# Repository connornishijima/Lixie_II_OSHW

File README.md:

# Lixie II Open Hardware
Want to make your own Lixie II? You're in the right place. This repository is a work in progress, but everything you need like the 3D printed base kit, Eagle PCB files or CAD files are here already!

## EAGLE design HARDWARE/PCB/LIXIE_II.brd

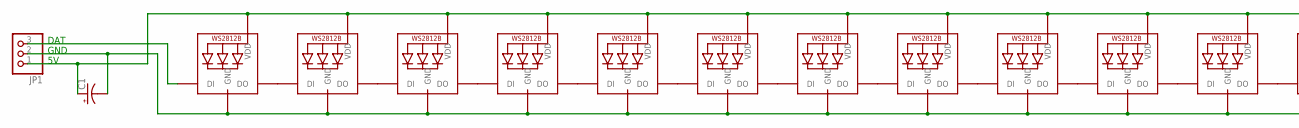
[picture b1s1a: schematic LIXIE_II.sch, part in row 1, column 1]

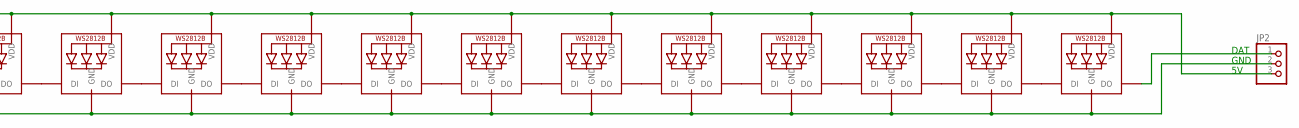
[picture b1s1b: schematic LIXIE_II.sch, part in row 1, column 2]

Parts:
C1: CPOL-USE5-10.5; E5-10,5
JP1, JP2: PINHD-1X3; 1X03
LED1, LED2, LED3, LED4, LED5, LED6, LED7, LED8, LED9, LED10, LED11, LED12, LED13, LED14, LED15, LED16, LED17, LED18, LED19, LED20, LED21, LED22: WS2812B_5050N; WS2812B-NARROW

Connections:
5V: C1.+, JP1.1, JP2.3, LED1.1-VDD (VDD), LED2.1-VDD (VDD), LED3.1-VDD (VDD), LED4.1-VDD (VDD), LED5.1-VDD (VDD), LED6.1-VDD (VDD), LED7.1-VDD (VDD), LED8.1-VDD (VDD), LED9.1-VDD (VDD), LED10.1-VDD (VDD), LED11.1-VDD (VDD), LED12.1-VDD (VDD), LED13.1-VDD (VDD), LED14.1-VDD (VDD), LED15.1-VDD (VDD), LED16.1-VDD (VDD), LED17.1-VDD (VDD), LED18.1-VDD (VDD), LED19.1-VDD (VDD), LED20.1-VDD (VDD), LED21.1-VDD (VDD), LED22.1-VDD (VDD)
GND: C1.-, JP1.2, JP2.2, LED1.3-GND (GND), LED2.3-GND (GND), LED3.3-GND (GND), LED4.3-GND (GND), LED5.3-GND (GND), LED6.3-GND (GND), LED7.3-GND (GND), LED8.3-GND (GND), LED9.3-GND (GND), LED10.3-GND (GND), LED11.3-GND (GND), LED12.3-GND (GND), LED13.3-GND (GND), LED14.3-GND (GND), LED15.3-GND (GND), LED16.3-GND (GND), LED17.3-GND (GND), LED18.3-GND (GND), LED19.3-GND (GND), LED20.3-GND (GND), LED21.3-GND (GND), LED22.3-GND (GND)
unnamed: JP1.3, LED1.4-DIN (DI)
unnamed: LED1.2-DOUT (DO), LED2.4-DIN (DI)
unnamed: LED2.2-DOUT (DO), LED3.4-DIN (DI)
unnamed: LED3.2-DOUT (DO), LED4.4-DIN (DI)
unnamed: LED4.2-DOUT (DO), LED5.4-DIN (DI)
unnamed: LED5.2-DOUT (DO), LED6.4-DIN (DI)
unnamed: LED6.2-DOUT (DO), LED7.4-DIN (DI)
unnamed: LED7.2-DOUT (DO), LED8.4-DIN (DI)
unnamed: LED8.2-DOUT (DO), LED9.4-DIN (DI)
unnamed: LED9.2-DOUT (DO), LED10.4-DIN (DI)
unnamed: LED10.2-DOUT (DO), LED11.4-DIN (DI)
unnamed: LED11.2-DOUT (DO), LED12.4-DIN (DI)
unnamed: LED12.2-DOUT (DO), LED13.4-DIN (DI)
unnamed: LED13.2-DOUT (DO), LED14.4-DIN (DI)
unnamed: LED14.2-DOUT (DO), LED15.4-DIN (DI)
unnamed: LED15.2-DOUT (DO), LED16.4-DIN (DI)
unnamed: LED16.2-DOUT (DO), LED17.4-DIN (DI)
unnamed: LED17.2-DOUT (DO), LED18.4-DIN (DI)
unnamed: LED18.2-DOUT (DO), LED19.4-DIN (DI)
unnamed: LED19.2-DOUT (DO), LED20.4-DIN (DI)
unnamed: LED20.2-DOUT (DO), LED21.4-DIN (DI)
unnamed: LED21.2-DOUT (DO), LED22.4-DIN (DI)
unnamed: JP2.1, LED22.2-DOUT (DO)

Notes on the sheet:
DAT
GND

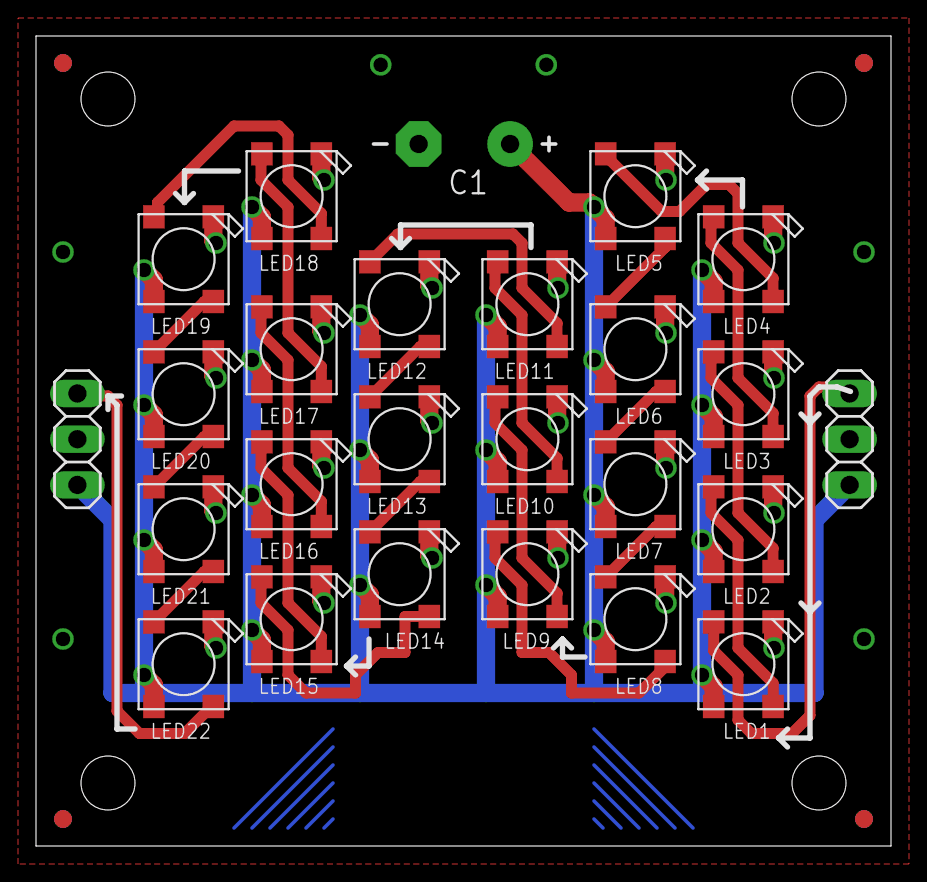
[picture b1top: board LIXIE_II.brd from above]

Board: 2 copper layers, 47.5 x 45.0 mm, 29 parts (0 on the bottom side), 25 nets.

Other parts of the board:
U$1, U$2, U$3, U$4: CIRCLE-1MM-2R

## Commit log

2019-08-13 Added 3D printing STLs
2019-08-13 Added Assembly Instructions
2019-11-22 Updated to improved base design!
2020-10-05 Added printable Lixie II Cap
